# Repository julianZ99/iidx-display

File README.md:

# IIDX Display

> **WIP** — PCB design complete, firmware and PC bridge not yet implemented.
> Untested — hardware not yet fabricated/assembled.

DIY 9-digit 16-segment display for beatmania IIDX and general PC use.

Reads the ticker from [spice2x](https://github.com/spice2x/spice2x.github.io) via its
TCP/JSON API (`ticker_get`) and displays it on 9x 16-segment digits.

## Hardware

- **MCU:** Waveshare RP2040 Zero
- **Drivers:** 2x HOLTEK HT16K33 (I2C LED matrix driver)
- **Displays:** 9x Kingbright PSC08-11SURKWA (0.8", red, common cathode, 16-segment)
- **Decimals:** 9x individual GPIO-driven decimal points

### Pinout

| Func | RP2040 GPIO |
|------|-------------|
| I2C SDA | GPIO0 |
| I2C SCL | GPIO1 |
| DP1-DP9 | GPIO2-GPIO10 |

### I2C Layout

Both HT16K33 share the same I2C bus. U1 drives displays 1-5 (COM0-COM4) and all 16
segment lines. U2 drives displays 6-9 (COM1-COM4) with ROW0-2 paralleled to U1 for
segments A/B/C (extra current drive).

U2 address is set via a diode+resistor network on the AD/COM0 pin.

### PCB

KiCad design files are in `pcb/`. Footprint library: `pcb/iidx-library.pretty/`.

## Architecture

```
┌──────────┐    TCP/JSON     ┌──────────────┐   USB Serial   ┌──────────────────┐
│  spice2x  │ ─────────────→ │ pc-bridge/   │ ─────────────→ │ RP2040 Zero      │
│  (-api)   │  ticker_get()  │ bridge.py    │  9 raw bytes   │   2× HT16K33     │
└──────────┘                 └──────────────┘                │   9× 16seg DPs   │
                                                              └──────────────────┘
```

The game ticker is 9 characters (`IIDXIO_LED_TICKER[10]` in spice2x's
`games/iidx/iidx.h`). The PC bridge polls `ticker_get()` via the TCP API and forwards
the string over USB serial to the Pico.

### Project Structure

```
├── pcb/                  KiCad design files
├── firmware/             Pico SDK C/C++ source
│   └── src/
│       ├── main.c        init, I2C, USB serial loop
│       ├── ht16k33.c     HT16K33 driver
│       ├── display.c     display buffer, font mapping
│       └── font_16seg.h  ASCII → 16-segment lookup
└── pc-bridge/
    └── bridge.py         spice2x API client → serial
```

## Firmware

C/C++ using the Raspberry Pi Pico SDK. Source in `firmware/`.

### Building

```bash
cd firmware
mkdir build && cd build
cmake ..
make
```

## PC Bridge

Python script that connects to spice2x's TCP API, polls `ticker_get()`, and forwards
the 9-character string over USB serial.

### spice2x Setup

Enable the API: `-api 1337 -apipass yourpass`

API request format (null-terminated JSON):

```json
{"id":1,"module":"iidx","function":"ticker_get","params":[]}
```

Response includes the 9-char ticker string in the `data` field.

## TODO

- [ ] Assemble and test first prototype
- [ ] Implement Pico firmware (I2C init, HT16K33 config, font table, USB serial)
- [ ] Implement PC bridge script (spice2x TCP API → serial)
- [ ] Test with spice2x `-api` ticker data

## License

MIT

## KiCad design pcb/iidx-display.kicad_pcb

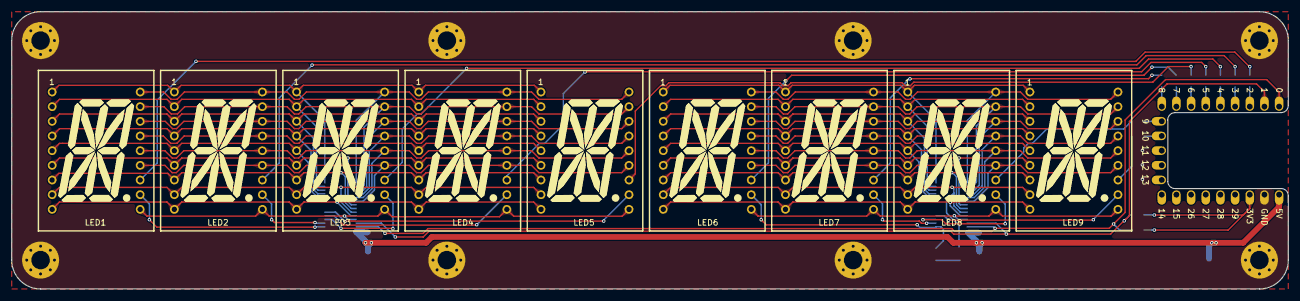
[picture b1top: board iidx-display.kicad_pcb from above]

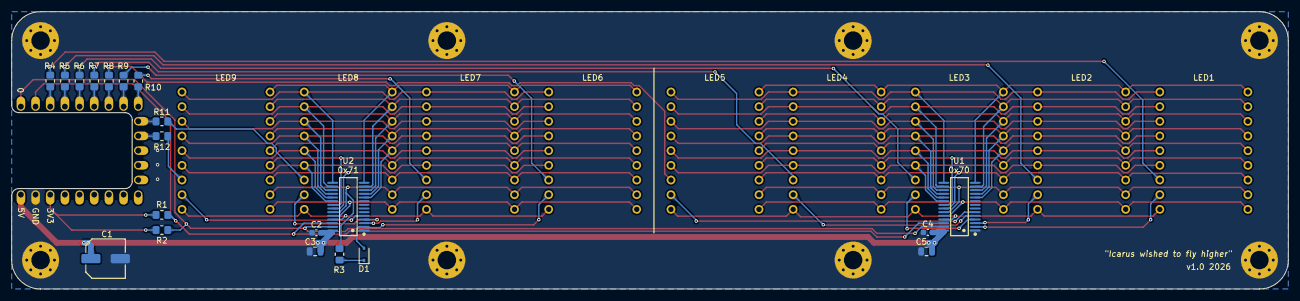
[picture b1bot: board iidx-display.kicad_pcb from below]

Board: 2 copper layers, 221.0 x 48.0 mm, 38 parts (20 on the bottom side), 65 nets.

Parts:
A1: rp2040 zero; RP2040_Zero_Castellated
C1: 47µF; C_Elec_6.3x5.4
C2, C4: 100nF; C_0603_1608Metric
C3, C5: 10µF; C_0805_2012Metric
D1: 1N4148WS; D_SOD-323
H1, H2, H3, H4, H5, H6, H7, H8: MountingHole_Pad; MountingHole_3.2mm_M3_Pad_Via
LED1, LED2, LED3, LED4, LED5, LED6, LED7, LED8, LED9: LED-SEG-TH_18P-L27.7-W19.9-P2.54-LS15.2_HDSP-3903
R1, R2: 4.7kΩ; R_0805_2012Metric_Pad1.20x1.40mm_HandSolder
R3: 39kΩ; R_0805_2012Metric_Pad1.20x1.40mm_HandSolder
R4, R5, R6, R7, R8, R9, R10, R11, R12: 330Ω; R_0805_2012Metric_Pad1.20x1.40mm_HandSolder
U1, U2: SSOP-28_L9.9-W3.9-P0.64-LS6.0-BL

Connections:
3v3: A1.21 (3V3), R1.2, R2.2
5v: A1.23 (5V), C1.1, C2.2, C3.2, C4.2, C5.2, U1.28 (VDD), U2.28 (VDD)
A0: LED6.8 (g), LED7.8 (g), LED8.8 (g), LED9.8 (g), R3.2, U2.23 (ROW2/A0)
AD: D1.2 (A), LED6.11 (C), U2.2 (COM0/AD)
D1 COM: LED1.11 (C), U1.2 (COM0/AD)
D2 COM: LED2.11 (C), U1.3 (COM1/KS0)
D3 COM: LED3.11 (C), U1.4 (COM2/KS1)
D4 COM: LED4.11 (C), U1.5 (COM3/KS2)
D5 COM: LED5.11 (C), U1.6 (COM4)
D7 COM: LED7.11 (C), U2.3 (COM1/KS0)
D8 COM: LED8.11 (C), U2.4 (COM2/KS1)
D9 COM: LED9.11 (C), U2.5 (COM3/KS2)
DP1: LED1.12 (DP), R4.2
DP2: LED2.12 (DP), R5.2
DP3: LED3.12 (DP), R6.2
DP4: LED4.12 (DP), R7.2
DP5: LED5.12 (DP), R8.2
DP6: LED6.12 (DP), R9.2
DP7: LED7.12 (DP), R10.2
DP8: LED8.12 (DP), R11.2
DP9: LED9.12 (DP), R12.2
GND: A1.22 (GND), C1.2, C2.1, C3.1, C4.1, C5.1, H1.1 (1_1), H2.1 (1_1), H3.1 (1_1), H4.1 (1_1), H5.1 (1_1), H6.1 (1_1), H7.1 (1_1), H8.1 (1_1), U1.1 (VSS), U2.1 (VSS)
GP2: A1.3 (2), R4.1
GP3: A1.4 (3), R5.1
GP4: A1.5 (4), R6.1
GP5: A1.6 (5), R7.1
GP6: A1.7 (6), R8.1
GP7: A1.8 (7), R9.1
GP8: A1.9 (8), R10.1
GP9: A1.10 (9), R11.1
GP10: A1.11 (10), R12.1
unnamed: D1.1 (K), R3.1
SCL: A1.2 (1), R1.1, U1.26 (SCL), U2.26 (SCL)
SDA: A1.1 (0), R2.1, U1.27 (SDA), U2.27 (SDA)
SEG A1: LED1.1 (a), LED2.1 (a), LED3.1 (a), LED4.1 (a), LED5.1 (a), U1.14 (ROW11/K9)
SEG A2: LED6.1 (a), LED7.1 (a), LED8.1 (a), LED9.1 (a), U2.14 (ROW11/K9)
SEG B1: LED1.18 (b), LED2.18 (b), LED3.18 (b), LED4.18 (b), LED5.18 (b), U1.15 (ROW10/K8)
SEG B2: LED6.18 (b), LED7.18 (b), LED8.18 (b), LED9.18 (b), U2.15 (ROW10/K8)
SEG C1: LED1.16 (c), LED2.16 (c), LED3.16 (c), LED4.16 (c), LED5.16 (c), U1.17 (ROW8/K6)
SEG C2: LED6.16 (c), LED7.16 (c), LED8.16 (c), LED9.16 (c), U2.17 (ROW8/K6)
SEG D1: LED1.13 (d), LED2.13 (d), LED3.13 (d), LED4.13 (d), LED5.13 (d), U1.20 (ROW5/K3)
SEG D2: LED6.13 (d), LED7.13 (d), LED8.13 (d), LED9.13 (d), U2.20 (ROW5/K3)
SEG E1: LED1.10 (e), LED2.10 (e), LED3.10 (e), LED4.10 (e), LED5.10 (e), U1.25 (ROW0/A2)
SEG E2: LED6.10 (e), LED7.10 (e), LED8.10 (e), LED9.10 (e), U2.25 (ROW0/A2)
SEG F1: LED1.9 (f), LED2.9 (f), LED3.9 (f), LED4.9 (f), LED5.9 (f), U1.24 (ROW1/A1)
SEG F2: LED6.9 (f), LED7.9 (f), LED8.9 (f), LED9.9 (f), U2.24 (ROW1/A1)
SEG G1: LED1.8 (g), LED2.8 (g), LED3.8 (g), LED4.8 (g), LED5.8 (g), U1.23 (ROW2/A0)
SEG H1: LED1.4 (h), LED2.4 (h), LED3.4 (h), LED4.4 (h), LED5.4 (h), U1.11 (ROW14/K12)
SEG H2: LED6.4 (h), LED7.4 (h), LED8.4 (h), LED9.4 (h), U2.11 (ROW14/K12)
SEG K1: LED1.3 (k), LED2.3 (k), LED3.3 (k), LED4.3 (k), LED5.3 (k), U1.12 (ROW13/K11)
SEG K2: LED6.3 (k), LED7.3 (k), LED8.3 (k), LED9.3 (k), U2.12 (ROW13/K11)
SEG M1: LED1.2 (m), LED2.2 (m), LED3.2 (m), LED4.2 (m), LED5.2 (m), U1.13 (ROW12/K10)
SEG M2: LED6.2 (m), LED7.2 (m), LED8.2 (m), LED9.2 (m), U2.13 (ROW12/K10)
SEG N1: LED1.17 (n), LED2.17 (n), LED3.17 (n), LED4.17 (n), LED5.17 (n), U1.16 (ROW9/K7)
SEG N2: LED6.17 (n), LED7.17 (n), LED8.17 (n), LED9.17 (n), U2.16 (ROW9/K7)
SEG P1: LED1.15 (p), LED2.15 (p), LED3.15 (p), LED4.15 (p), LED5.15 (p), U1.18 (ROW7/K5)
SEG P2: LED6.15 (p), LED7.15 (p), LED8.15 (p), LED9.15 (p), U2.18 (ROW7/K5)
SEG R1: LED1.14 (r), LED2.14 (r), LED3.14 (r), LED4.14 (r), LED5.14 (r), U1.19 (ROW6/K4)
SEG R2: LED6.14 (r), LED7.14 (r), LED8.14 (r), LED9.14 (r), U2.19 (ROW6/K4)
SEG S1: LED1.6 (s), LED2.6 (s), LED3.6 (s), LED4.6 (s), LED5.6 (s), U1.21 (ROW4/K2)
SEG S2: LED6.6 (s), LED7.6 (s), LED8.6 (s), LED9.6 (s), U2.21 (ROW4/K2)
SEG T1: LED1.7 (t), LED2.7 (t), LED3.7 (t), LED4.7 (t), LED5.7 (t), U1.22 (ROW3/K1)
SEG T2: LED6.7 (t), LED7.7 (t), LED8.7 (t), LED9.7 (t), U2.22 (ROW3/K1)
SEG U1: LED1.5 (u), LED2.5 (u), LED3.5 (u), LED4.5 (u), LED5.5 (u), U1.10 (ROW15/K13/INT)
SEG U2: LED6.5 (u), LED7.5 (u), LED8.5 (u), LED9.5 (u), U2.10 (ROW15/K13/INT)

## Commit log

2026-05-20 fix: update readme status
2026-05-20 fix: readme formatting
